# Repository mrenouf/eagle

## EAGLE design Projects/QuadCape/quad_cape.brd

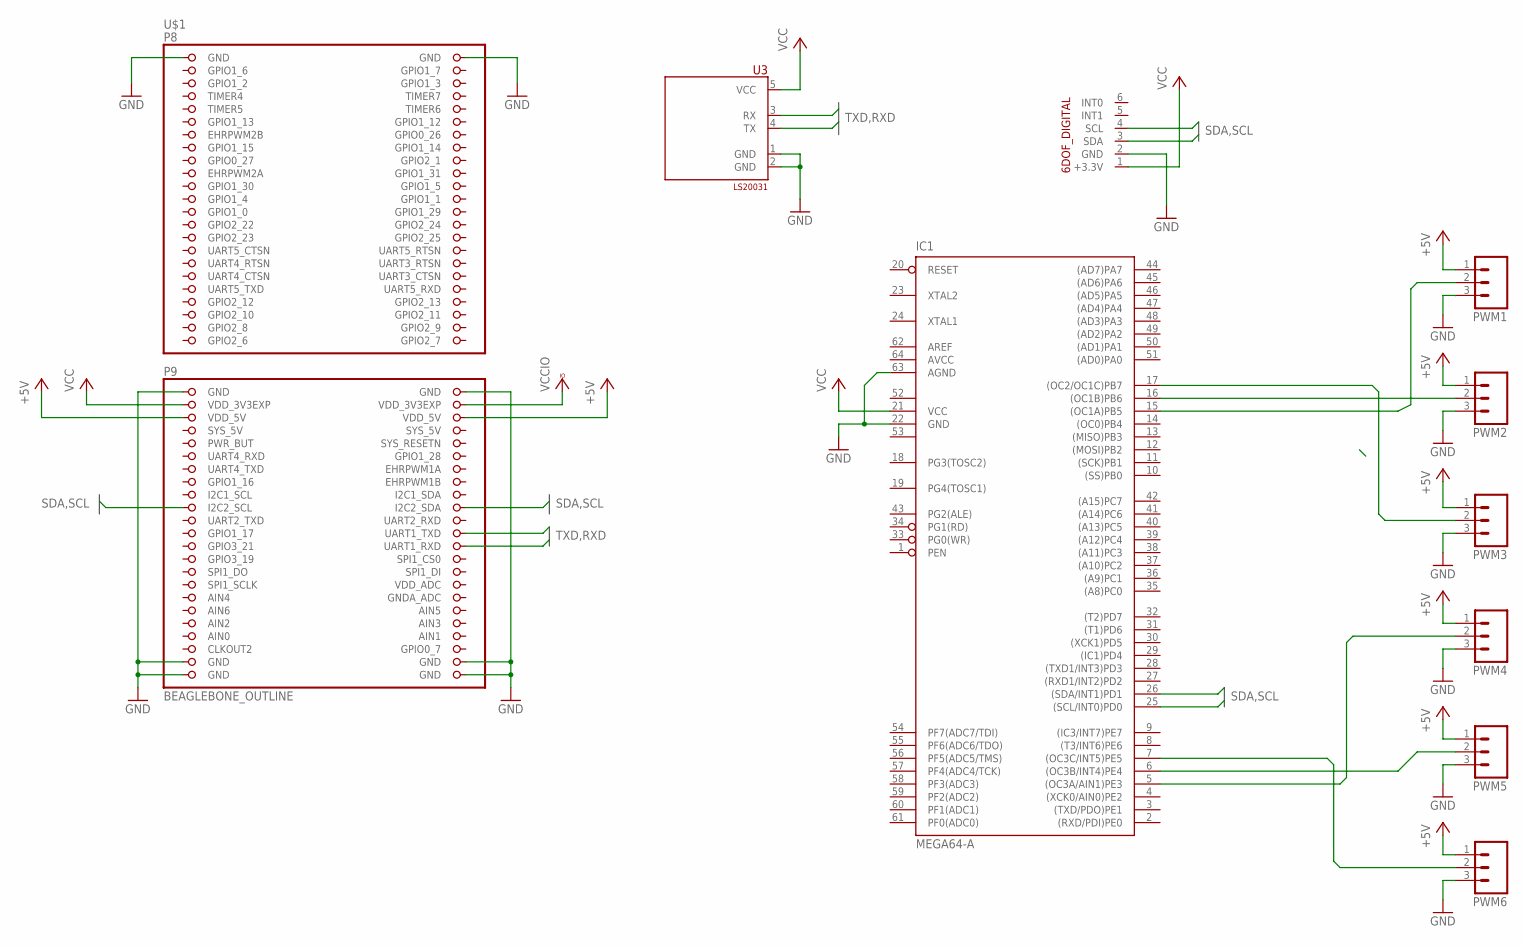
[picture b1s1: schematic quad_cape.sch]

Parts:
IC1: MEGA64-A; TQFP64
PWM1, PWM2, PWM3, PWM4, PWM5, PWM6: M03; JST-3-SMD
U3: LS20031
U$1: BEAGLEBONE_OUTLINE; BEAGLEBONE_SHIELD
U$2: 6DOF-DIGITAL; 6DOF_DIGITAL_V10

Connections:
+5V: PWM1.1, PWM2.1, PWM3.1, PWM4.1, PWM5.1, PWM6.1, U$1.51 (VDD_5V), U$1.52 (VDD_5V)
AIN0: U$1.85 (AIN0)
AIN3: U$1.84 (AIN3)
GND: IC1.22 (GND), IC1.63 (AGND), PWM1.3, PWM2.3, PWM3.3, PWM4.3, PWM5.3, PWM6.3, U3.1 (GND), U3.2 (GND), U$1.1 (GND), U$1.2 (GND), U$1.47 (GND), U$1.48 (GND), U$1.89 (GND), U$1.90 (GND), U$1.91 (GND), U$1.92 (GND), U$2.2 (GND)
GND1: IC1.53 (GND1)
GPIO1_6: U$1.3 (GPIO1_6)
GPIO1_7: U$1.4 (GPIO1_7)
GPIO2_6: U$1.45 (GPIO2_6)
GPIO2_7: U$1.46 (GPIO2_7)
GPIO2_8: U$1.43 (GPIO2_8)
GPIO2_9: U$1.44 (GPIO2_9)
GPIO2_11: U$1.42 (GPIO2_11)
PWM1: IC1.15 ((OC1A)PB5), PWM1.2
PWM2: IC1.16 ((OC1B)PB6), PWM2.2
PWM3: IC1.17 ((OC2/OC1C)PB7), PWM3.2
PWM4: IC1.5 ((OC3A/AIN1)PE3), PWM4.2
PWM5: IC1.6 ((OC3B/INT4)PE4), PWM5.2
PWM6: IC1.7 ((OC3C/INT5)PE5), PWM6.2
RXD: U3.4 (TX), U$1.72 (UART1_RXD)
SCL: IC1.25 ((SCL/INT0)PD0), U$1.65 (I2C2_SCL), U$2.4 (SCL)
SDA: IC1.26 ((SDA/INT1)PD1), U$1.66 (I2C2_SDA), U$2.3 (SDA)
TXD: U3.3 (RX), U$1.70 (UART1_TXD)
VCC: IC1.21 (VCC), U3.5 (VCC), U$1.49 (VDD_3V3EXP), U$2.1 (+3.3V)
VCC1: IC1.52 (VCC1)
VCCIO: U$1.50 (VDD_3V3EXP)

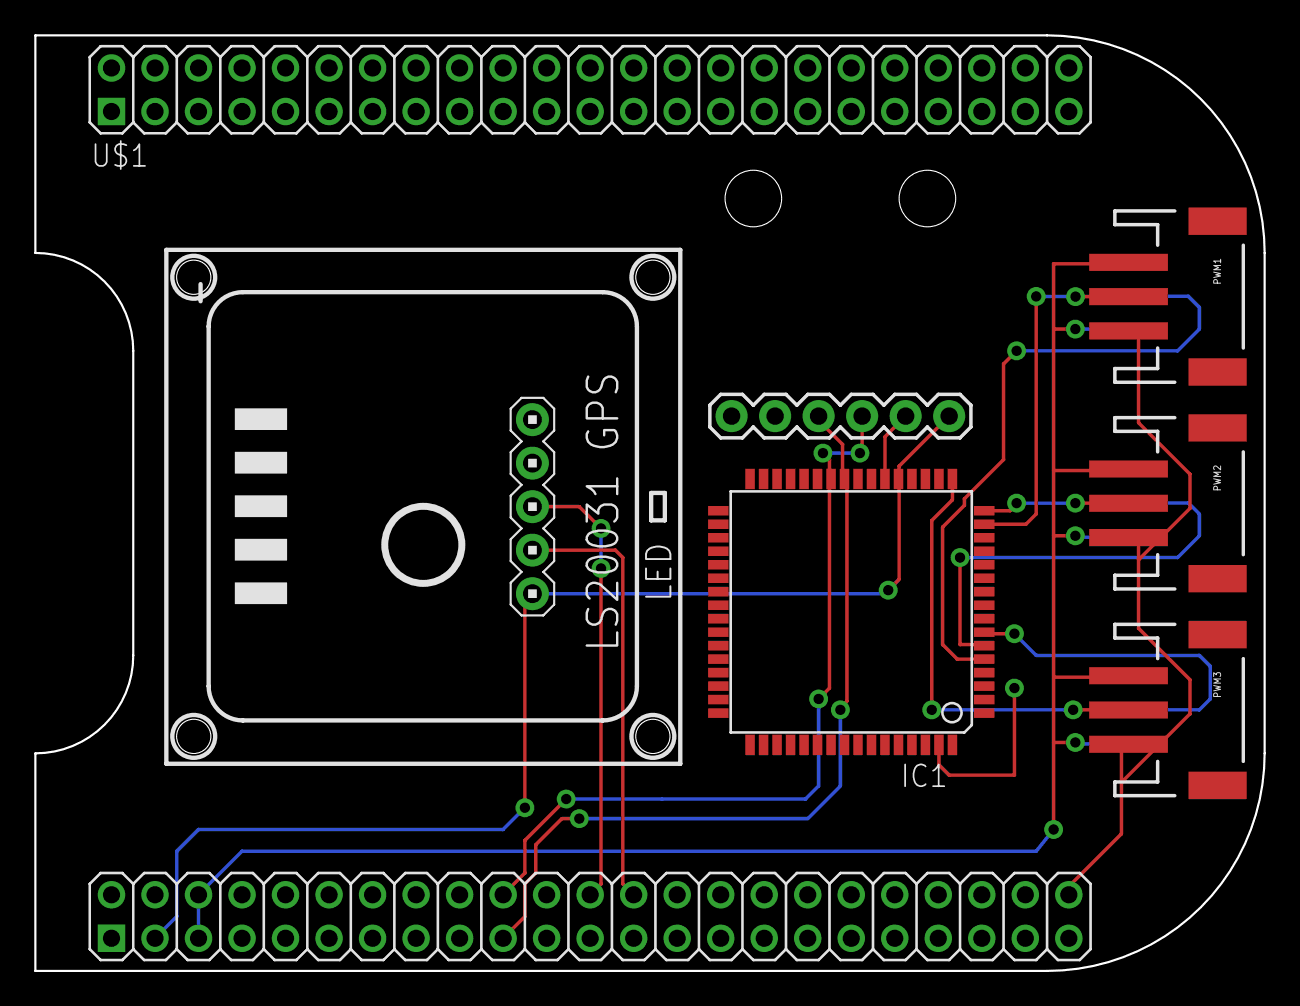
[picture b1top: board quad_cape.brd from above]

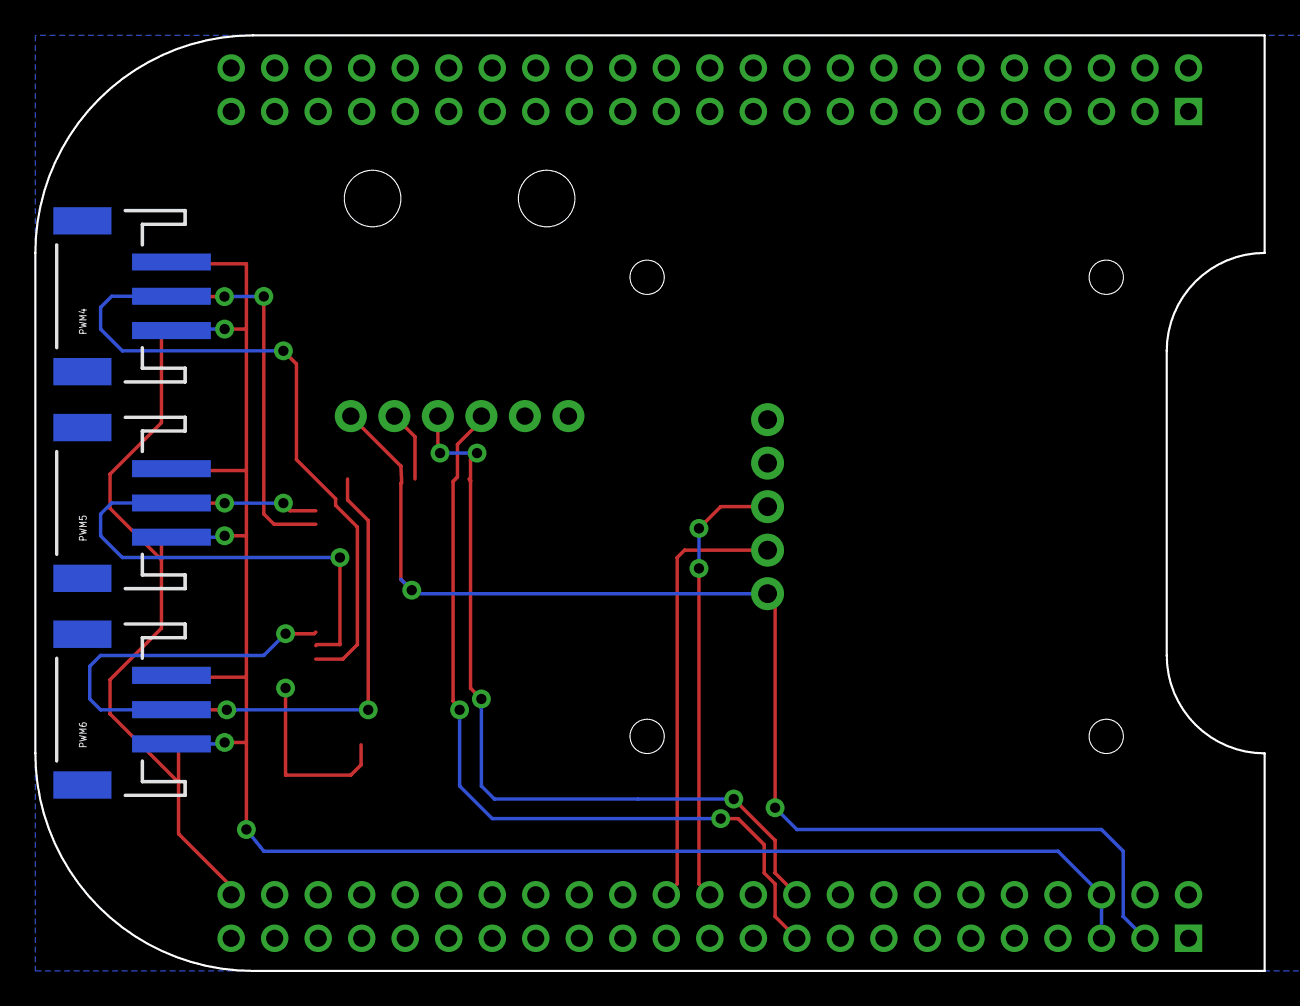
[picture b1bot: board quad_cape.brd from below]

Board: 2 copper layers, 71.8 x 54.6 mm, 10 parts (3 on the bottom side), 13 nets.

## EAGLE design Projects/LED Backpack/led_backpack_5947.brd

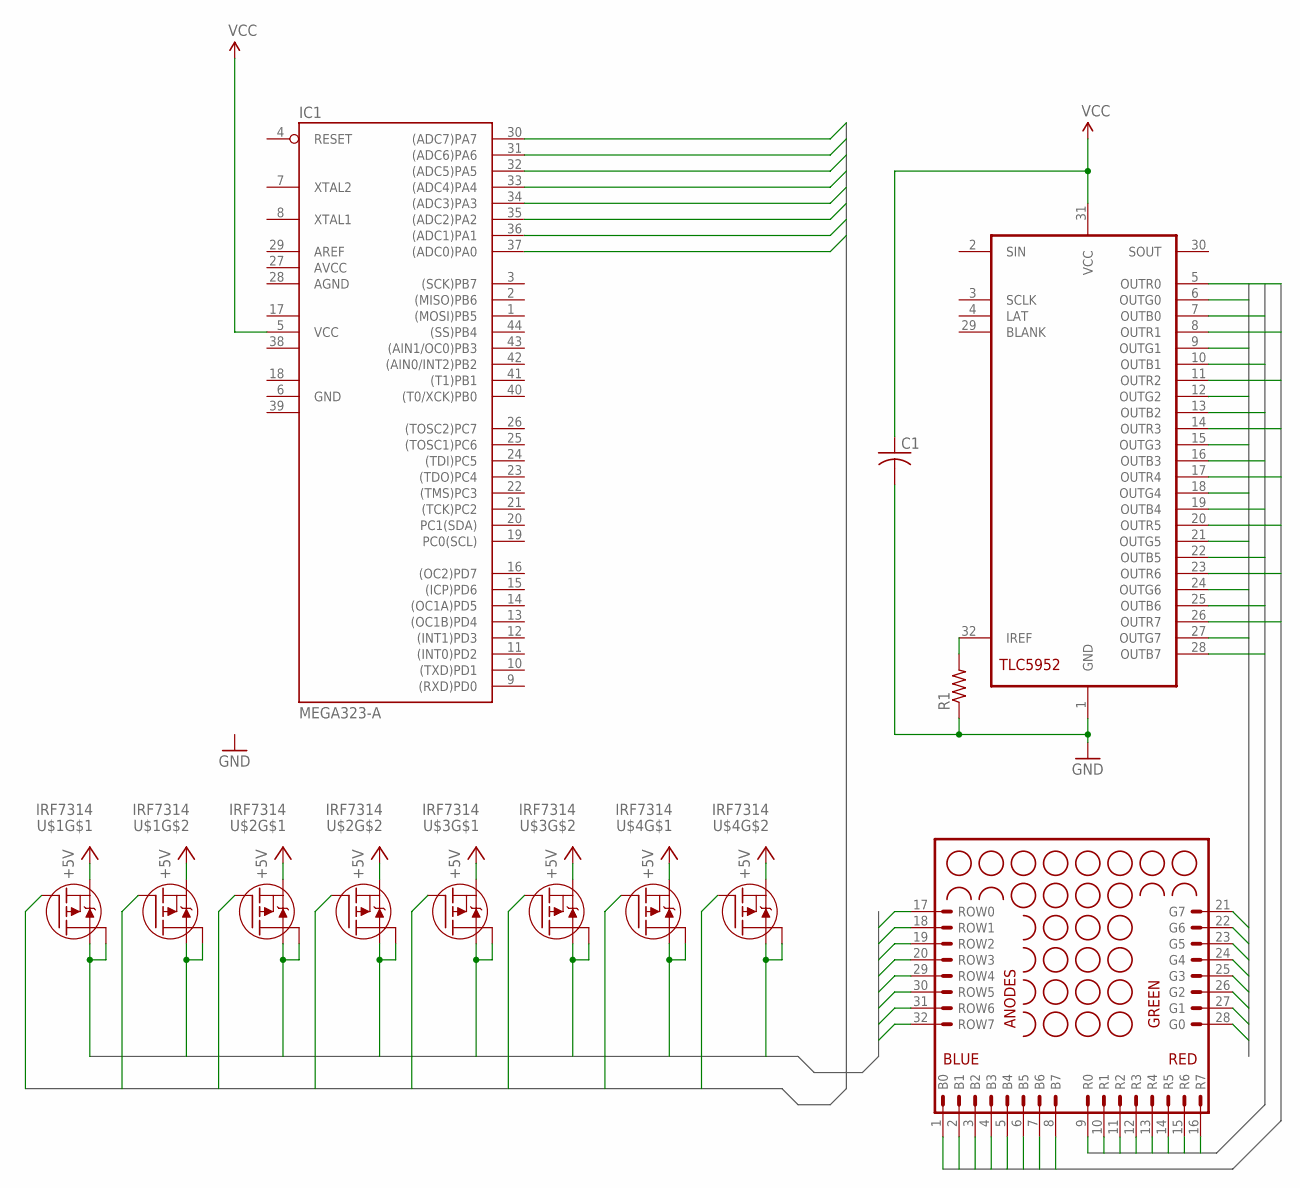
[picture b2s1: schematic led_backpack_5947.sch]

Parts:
C1: C-USC1206; C1206
IC1: MEGA323-A; TQFP44
MX1: MATRIX_8X8_TRICOLOR_ANODE_ROW; MATRIX_60MM_32PIN
R1: R-US_M1206; M1206
U$1, U$2, U$3, U$4: IRF7314; SO08
U$5: TLC5952; HTSSOP32DAP

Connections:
+5V: U$1.1 (S), U$1.3 (S), U$2.1 (S), U$2.3 (S), U$3.1 (S), U$3.3 (S), U$4.1 (S), U$4.3 (S)
AGND: IC1.28 (AGND)
AREF: IC1.29 (AREF)
AVCC: IC1.27 (AVCC)
B0: MX1.1 (B0), U$5.7 (OUTB0)
B1: MX1.2 (B1), U$5.10 (OUTB1)
B2: MX1.3 (B2), U$5.13 (OUTB2)
B3: MX1.4 (B3), U$5.16 (OUTB3)
B4: MX1.5 (B4), U$5.19 (OUTB4)
B5: MX1.6 (B5), U$5.22 (OUTB5)
B6: MX1.7 (B6), U$5.25 (OUTB6)
B7: MX1.8 (B7), U$5.28 (OUTB7)
G0: MX1.28 (G0), U$5.6 (OUTG0)
G1: MX1.27 (G1), U$5.9 (OUTG1)
G2: MX1.26 (G2), U$5.12 (OUTG2)
G3: MX1.25 (G3), U$5.15 (OUTG3)
G4: MX1.24 (G4), U$5.18 (OUTG4)
G5: MX1.23 (G5), U$5.21 (OUTG5)
G6: MX1.22 (G6), U$5.24 (OUTG6)
G7: MX1.21 (G7), U$5.27 (OUTG7)
GND: C1.2, IC1.6 (GND), R1.1, U$5.1 (GND)
GND1: IC1.18 (GND1)
GND2: IC1.39 (GND2)
unnamed: R1.2, U$5.32 (IREF)
R0: MX1.9 (R0), U$5.5 (OUTR0)
R1: MX1.10 (R1), U$5.8 (OUTR1)
R2: MX1.11 (R2), U$5.11 (OUTR2)
R3: MX1.12 (R3), U$5.14 (OUTR3)
R4: MX1.13 (R4), U$5.17 (OUTR4)
R5: MX1.14 (R5), U$5.20 (OUTR5)
R6: MX1.15 (R6), U$5.23 (OUTR6)
R7: MX1.16 (R7), U$5.26 (OUTR7)
ROW_IN0: IC1.30 ((ADC7)PA7), U$1.2 (G)
ROW_IN1: IC1.31 ((ADC6)PA6), U$1.4 (G)
ROW_IN2: IC1.32 ((ADC5)PA5), U$2.2 (G)
ROW_IN3: IC1.33 ((ADC4)PA4), U$2.4 (G)
ROW_IN4: IC1.34 ((ADC3)PA3), U$3.2 (G)
ROW_IN5: IC1.35 ((ADC2)PA2), U$3.4 (G)
ROW_IN6: IC1.36 ((ADC1)PA1), U$4.2 (G)
ROW_IN7: IC1.37 ((ADC0)PA0), U$4.4 (G)
ROW_OUT0: MX1.17 (ROW0), U$1.7 (D), U$1.8 (D)
ROW_OUT1: MX1.18 (ROW1), U$1.5 (D), U$1.6 (D)
ROW_OUT2: MX1.19 (ROW2), U$2.7 (D), U$2.8 (D)
ROW_OUT3: MX1.20 (ROW3), U$2.5 (D), U$2.6 (D)
ROW_OUT4: MX1.29 (ROW4), U$3.7 (D), U$3.8 (D)
ROW_OUT5: MX1.30 (ROW5), U$3.5 (D), U$3.6 (D)
ROW_OUT6: MX1.31 (ROW6), U$4.7 (D), U$4.8 (D)
ROW_OUT7: MX1.32 (ROW7), U$4.5 (D), U$4.6 (D)
VCC: C1.1, IC1.5 (VCC), U$5.31 (VCC)
VCC1: IC1.17 (VCC1)
VCC2: IC1.38 (VCC2)

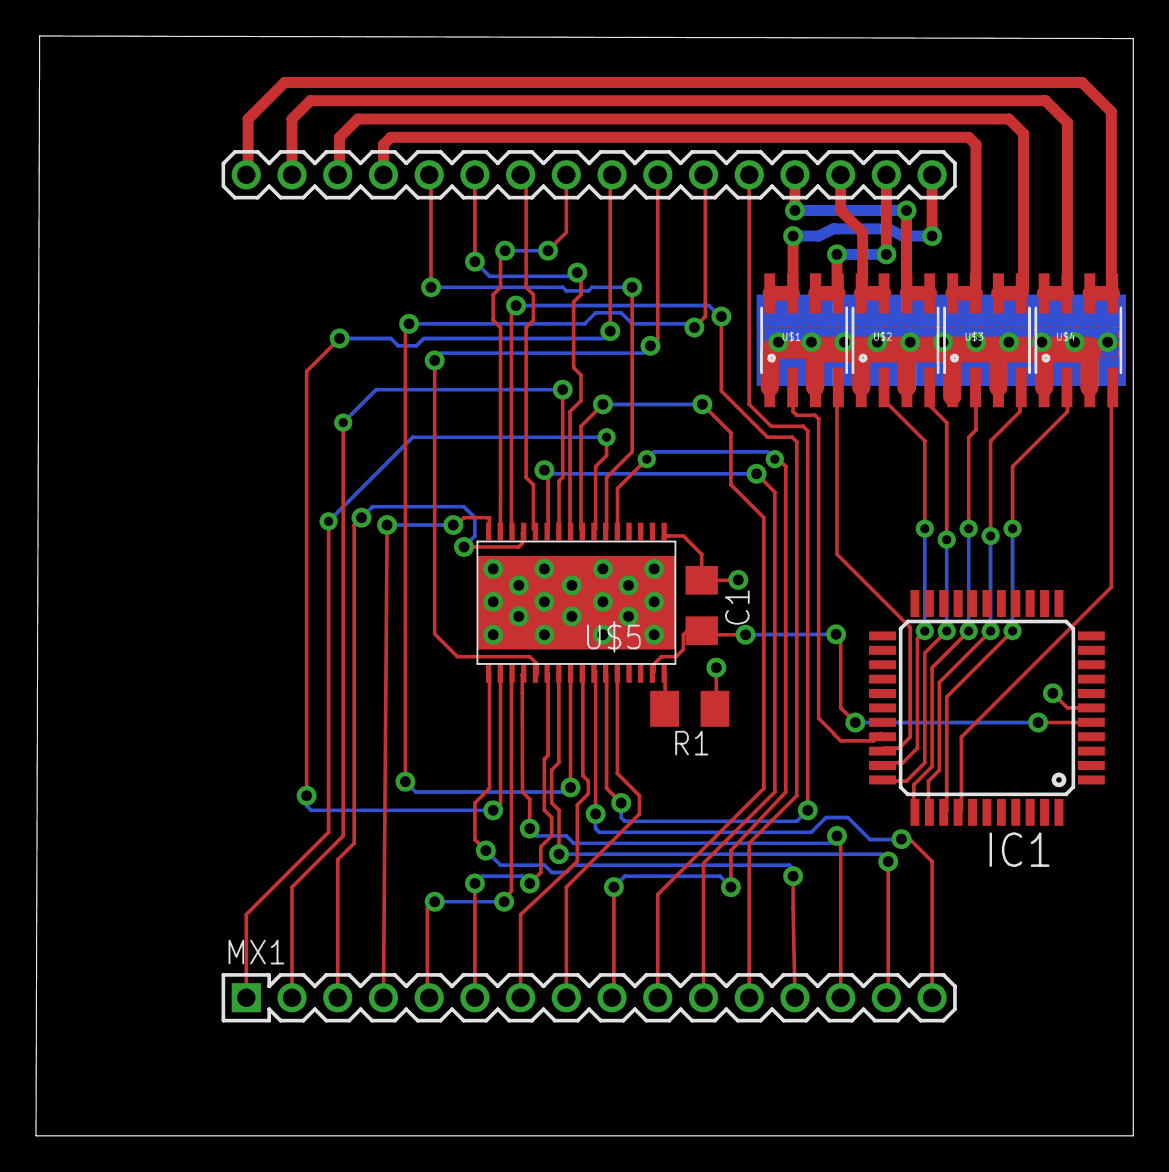
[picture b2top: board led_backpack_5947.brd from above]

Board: 2 copper layers, 61.0 x 61.1 mm, 9 parts (0 on the bottom side), 44 nets.

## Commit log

2012-03-03 My Eagle repo
2012-03-03 Merged with origin Eagle workdir
2012-03-03 Adding Adafruit and Sparkfun libraries as submodules
2012-03-04 Added ATMega328P
2012-03-04 Added pdf for ATMega328
2012-03-04 Began wiring up some connections
2012-03-04 Add supply to 'default' libraries
2012-03-04 Swapped symbol for Mega328 for a better on I had already made a while ago (oops)
2012-07-07 Sync
2012-07-11 Added TLC5952
2012-07-11 Imported better MEGA328P
2012-07-11 Added footprint for 6DOF-Digital module
2012-07-11 Sparkfun 6DOF Digital IMU
2012-07-11 Updated to TLC5952 and rerouted a lot of stuff
2012-07-11 Replaced individual Compass and Gyro with Sparkfun 6DOF-Digital module

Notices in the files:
parts and their libraries:
SparkFun-Connectors: Licensing: CC v3.0 Share-Alike You are welcome to use this library for commercial purposes.
